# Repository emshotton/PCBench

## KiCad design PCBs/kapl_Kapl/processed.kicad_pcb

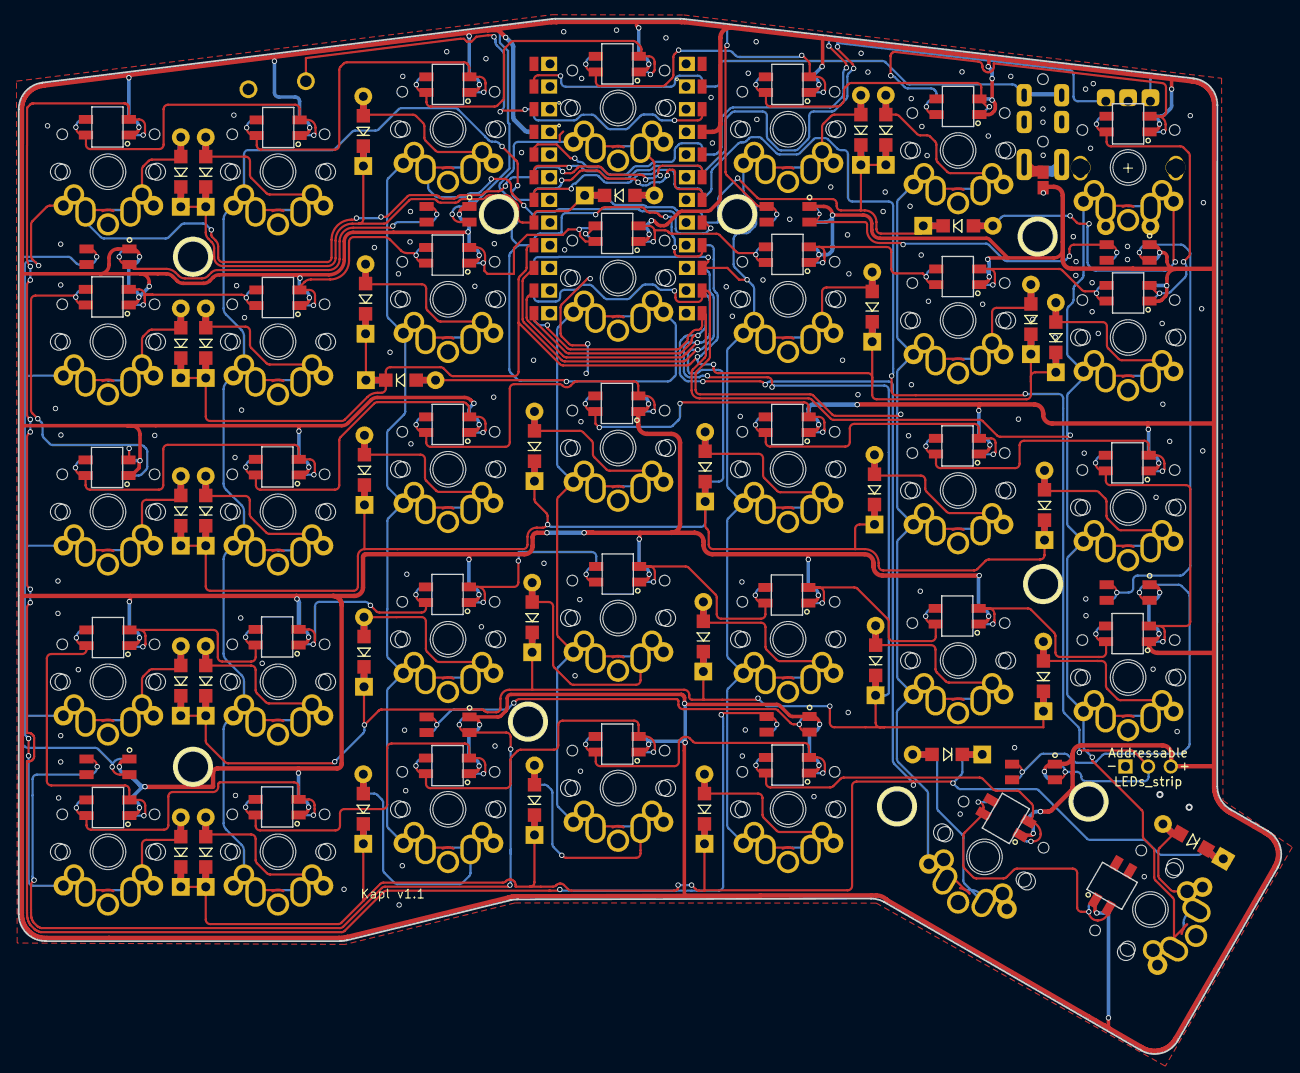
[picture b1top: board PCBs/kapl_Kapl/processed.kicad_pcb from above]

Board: 2 copper layers, 141.5 x 116.0 mm, 128 parts (0 on the bottom side), 97 nets.

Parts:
BL1, BL2, BL3, BL4, BL5, BL6, BL7, BL8, BL9: SK6812MINI; SK6812MINI_surface
D1, D2, D3, D4, D5, D6, D7, D8, D9, D10, D11, D12, D13, D14, D15, D16, D17, D18, D19, D20, D21, D22, D23, D24, D25, D26, D27, D28, D29, D30, D31, D32, D33, D34, D35: Diode
E_SW1: RotaryEncoder_Switch; RotaryEncoder_Alps_EC11E-Switch_Vertical_H20mm
H1, H2, H3, H4, H5, H6, H7, H8, H9: MountingHole; MountingHole_3.2mm_M3
J1: LED_strip_conector; StripLED_rev
L1, L2, L3, L4, L5, L6, L7, L8, L9, L10, L11, L12, L13, L14, L15, L16, L17, L18, L19, L20, L21, L22, L23, L24, L25, L26, L27, L28, L29, L30, L31, L32, L33, L34, L35: SK6812MINI; SK6812MINI_rev
MJ1: Mini Jack; MJ-4PP-9
RSW1: SW_PUSH; ResetSW
SW1, SW2, SW3, SW4, SW5, SW6, SW8, SW9, SW10, SW11, SW12, SW13, SW14, SW15, SW16, SW17, SW18, SW19, SW20, SW21, SW22, SW23, SW24, SW25, SW26, SW27, SW28, SW29, SW30, SW31, SW32, SW33, SW34, SW35: SW_PUSH; MX-ALPs-PG1350-rev
SW7: SW_PUSH; MX-ALPs-PG1350-rev(for_encoder)
U1: ProMicro

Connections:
GND: BL1.2 (GND), BL2.2 (GND), BL3.2 (GND), BL4.2 (GND), BL5.2 (GND), BL6.2 (GND), BL7.2 (GND), BL8.2 (GND), BL9.2 (GND), E_SW1.C, J1.1, L1.2 (GND), L2.2 (GND), L3.2 (GND), L4.2 (GND), L5.2 (GND), L6.2 (GND), L7.2 (GND), L8.2 (GND), L9.2 (GND), L10.2 (GND), L11.2 (GND), L12.2 (GND), L13.2 (GND), L14.2 (GND), L15.2 (GND), L16.2 (GND), L17.2 (GND), L18.2 (GND), L19.2 (GND), L20.2 (GND), L21.2 (GND), L22.2 (GND), L23.2 (GND), L24.2 (GND), L25.2 (GND), L26.2 (GND), L27.2 (GND), L28.2 (GND), L29.2 (GND), L30.2 (GND), L31.2 (GND), L32.2 (GND), L33.2 (GND), L34.2 (GND), L35.2 (GND), MJ1.C, RSW1.2, U1.3 (GND), U1.4 (GND), U1.23 (GND)
LED: BL1.3 (DIN), J1.2, U1.7 (D4)
unnamed: BL1.1 (DOUT), BL2.3 (DIN)
unnamed: BL2.1 (DOUT), BL3.3 (DIN)
unnamed: BL3.1 (DOUT), BL4.3 (DIN)
unnamed: BL4.1 (DOUT), BL5.3 (DIN)
unnamed: BL5.1 (DOUT), BL6.3 (DIN)
unnamed: BL6.1 (DOUT), BL7.3 (DIN)
unnamed: BL7.1 (DOUT), BL8.3 (DIN)
unnamed: BL8.1 (DOUT), BL9.3 (DIN)
unnamed: BL9.1 (DOUT), L1.3 (DIN)
unnamed: D1.2 (A), SW1.2
unnamed: D2.2 (A), SW2.2
unnamed: D3.2 (A), SW3.2
unnamed: D4.2 (A), SW4.2
unnamed: D5.2 (A), SW5.2
unnamed: D6.2 (A), SW6.2
unnamed: D7.2 (A), E_SW1.S1, SW7.2
unnamed: D8.2 (A), SW8.2
unnamed: D9.2 (A), SW9.2
unnamed: D10.2 (A), SW10.2
unnamed: D11.2 (A), SW11.2
unnamed: D12.2 (A), SW12.2
unnamed: D13.2 (A), SW13.2
unnamed: D14.2 (A), SW14.2
unnamed: D15.2 (A), SW15.2
unnamed: D16.2 (A), SW16.2
unnamed: D17.2 (A), SW17.2
unnamed: D18.2 (A), SW18.2
unnamed: D19.2 (A), SW19.2
unnamed: D20.2 (A), SW20.2
unnamed: D21.2 (A), SW21.2
unnamed: D22.2 (A), SW22.2
unnamed: D23.2 (A), SW23.2
unnamed: D24.2 (A), SW24.2
unnamed: D25.2 (A), SW25.2
unnamed: D26.2 (A), SW26.2
unnamed: D27.2 (A), SW27.2
unnamed: D28.2 (A), SW28.2
unnamed: D29.2 (A), SW29.2
unnamed: D30.2 (A), SW30.2
unnamed: D31.2 (A), SW31.2
unnamed: D32.2 (A), SW32.2
unnamed: D33.2 (A), SW33.2
unnamed: D34.2 (A), SW34.2
unnamed: D35.2 (A), SW35.2
unnamed: L1.1 (DOUT), L2.3 (DIN)
unnamed: L2.1 (DOUT), L3.3 (DIN)
unnamed: L3.1 (DOUT), L4.3 (DIN)
unnamed: L4.1 (DOUT), L5.3 (DIN)
unnamed: L5.1 (DOUT), L6.3 (DIN)
unnamed: L6.1 (DOUT), L7.3 (DIN)
unnamed: L8.3 (DIN), L9.1 (DOUT)
unnamed: L9.3 (DIN), L10.1 (DOUT)
unnamed: L10.3 (DIN), L11.1 (DOUT)
unnamed: L11.3 (DIN), L12.1 (DOUT)
unnamed: L12.3 (DIN), L13.1 (DOUT)
unnamed: L13.3 (DIN), L14.1 (DOUT)
unnamed: L7.1 (DOUT), L14.3 (DIN)
unnamed: L15.1 (DOUT), L16.3 (DIN)
unnamed: L8.1 (DOUT), L15.3 (DIN)
unnamed: L16.1 (DOUT), L17.3 (DIN)
unnamed: L17.1 (DOUT), L18.3 (DIN)
unnamed: L18.1 (DOUT), L19.3 (DIN)
unnamed: L19.1 (DOUT), L20.3 (DIN)
unnamed: L20.1 (DOUT), L21.3 (DIN)
unnamed: L21.1 (DOUT), L28.3 (DIN)
unnamed: L22.1 (DOUT), L29.3 (DIN)
unnamed: L22.3 (DIN), L23.1 (DOUT)
unnamed: L23.3 (DIN), L24.1 (DOUT)
unnamed: L24.3 (DIN), L25.1 (DOUT)
unnamed: L25.3 (DIN), L26.1 (DOUT)
unnamed: L26.3 (DIN), L27.1 (DOUT)
unnamed: L27.3 (DIN), L28.1 (DOUT)
unnamed: L29.1 (DOUT), L30.3 (DIN)
unnamed: L30.1 (DOUT), L31.3 (DIN)
unnamed: L31.1 (DOUT), L32.3 (DIN)
unnamed: L32.1 (DOUT), L33.3 (DIN)
unnamed: L33.1 (DOUT), L34.3 (DIN)
unnamed: L34.1 (DOUT), L35.3 (DIN)
VCC: BL1.4 (VDD), BL2.4 (VDD), BL3.4 (VDD), BL4.4 (VDD), BL5.4 (VDD), BL6.4 (VDD), BL7.4 (VDD), BL8.4 (VDD), BL9.4 (VDD), J1.3, L1.4 (VDD), L2.4 (VDD), L3.4 (VDD), L4.4 (VDD), L5.4 (VDD), L6.4 (VDD), L7.4 (VDD), L8.4 (VDD), L9.4 (VDD), L10.4 (VDD), L11.4 (VDD), L12.4 (VDD), L13.4 (VDD), L14.4 (VDD), L15.4 (VDD), L16.4 (VDD), L17.4 (VDD), L18.4 (VDD), L19.4 (VDD), L20.4 (VDD), L21.4 (VDD), L22.4 (VDD), L23.4 (VDD), L24.4 (VDD), L25.4 (VDD), L26.4 (VDD), L27.4 (VDD), L28.4 (VDD), L29.4 (VDD), L30.4 (VDD), L31.4 (VDD), L32.4 (VDD), L33.4 (VDD), L34.4 (VDD), L35.4 (VDD), MJ1.D, U1.21 (VCC)
col0: SW1.1, SW8.1, SW15.1, SW22.1, SW29.1, U1.19 (F5)
col1: SW2.1, SW9.1, SW16.1, SW23.1, SW30.1, U1.18 (F6)
col2: SW3.1, SW10.1, SW17.1, SW24.1, SW31.1, U1.17 (F7)
col3: SW4.1, SW11.1, SW18.1, SW25.1, SW32.1, U1.16 (B1)
col4: SW5.1, SW12.1, SW19.1, SW26.1, SW33.1, U1.15 (B3)
col5: SW6.1, SW13.1, SW20.1, SW27.1, SW34.1, U1.14 (B2)
col6: E_SW1.S2, SW7.1, SW14.1, SW21.1, SW28.1, SW35.1, U1.13 (B6)
data: MJ1.B, U1.2 (RX)
encoder_A: E_SW1.A, U1.5 (SDA)
encoder_B: E_SW1.B, U1.6 (SCL)
reset: RSW1.1, U1.22 (RST)
row0: D1.1 (K), D2.1 (K), D3.1 (K), D4.1 (K), D5.1 (K), D6.1 (K), D7.1 (K), U1.8 (C6)
row1: D8.1 (K), D9.1 (K), D10.1 (K), D11.1 (K), D12.1 (K), D13.1 (K), D14.1 (K), U1.9 (D7)
row2: D15.1 (K), D16.1 (K), D17.1 (K), D18.1 (K), D19.1 (K), D20.1 (K), D21.1 (K), U1.10 (E6)
row3: D22.1 (K), D23.1 (K), D24.1 (K), D25.1 (K), D26.1 (K), D27.1 (K), D28.1 (K), U1.11 (B4)
row4: D29.1 (K), D30.1 (K), D31.1 (K), D32.1 (K), D33.1 (K), D34.1 (K), D35.1 (K), U1.12 (B5)

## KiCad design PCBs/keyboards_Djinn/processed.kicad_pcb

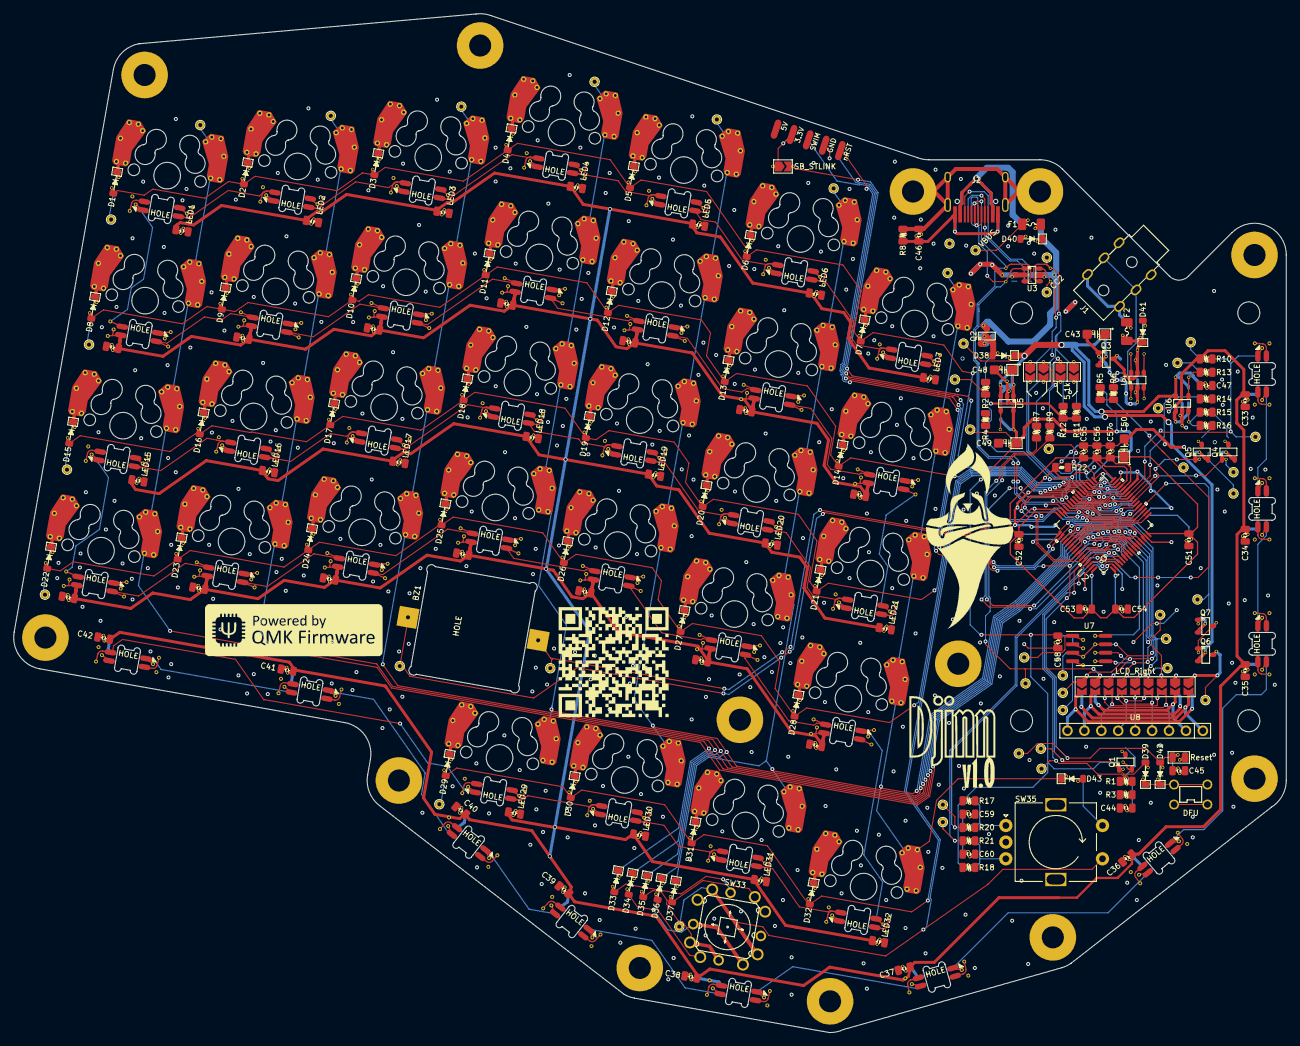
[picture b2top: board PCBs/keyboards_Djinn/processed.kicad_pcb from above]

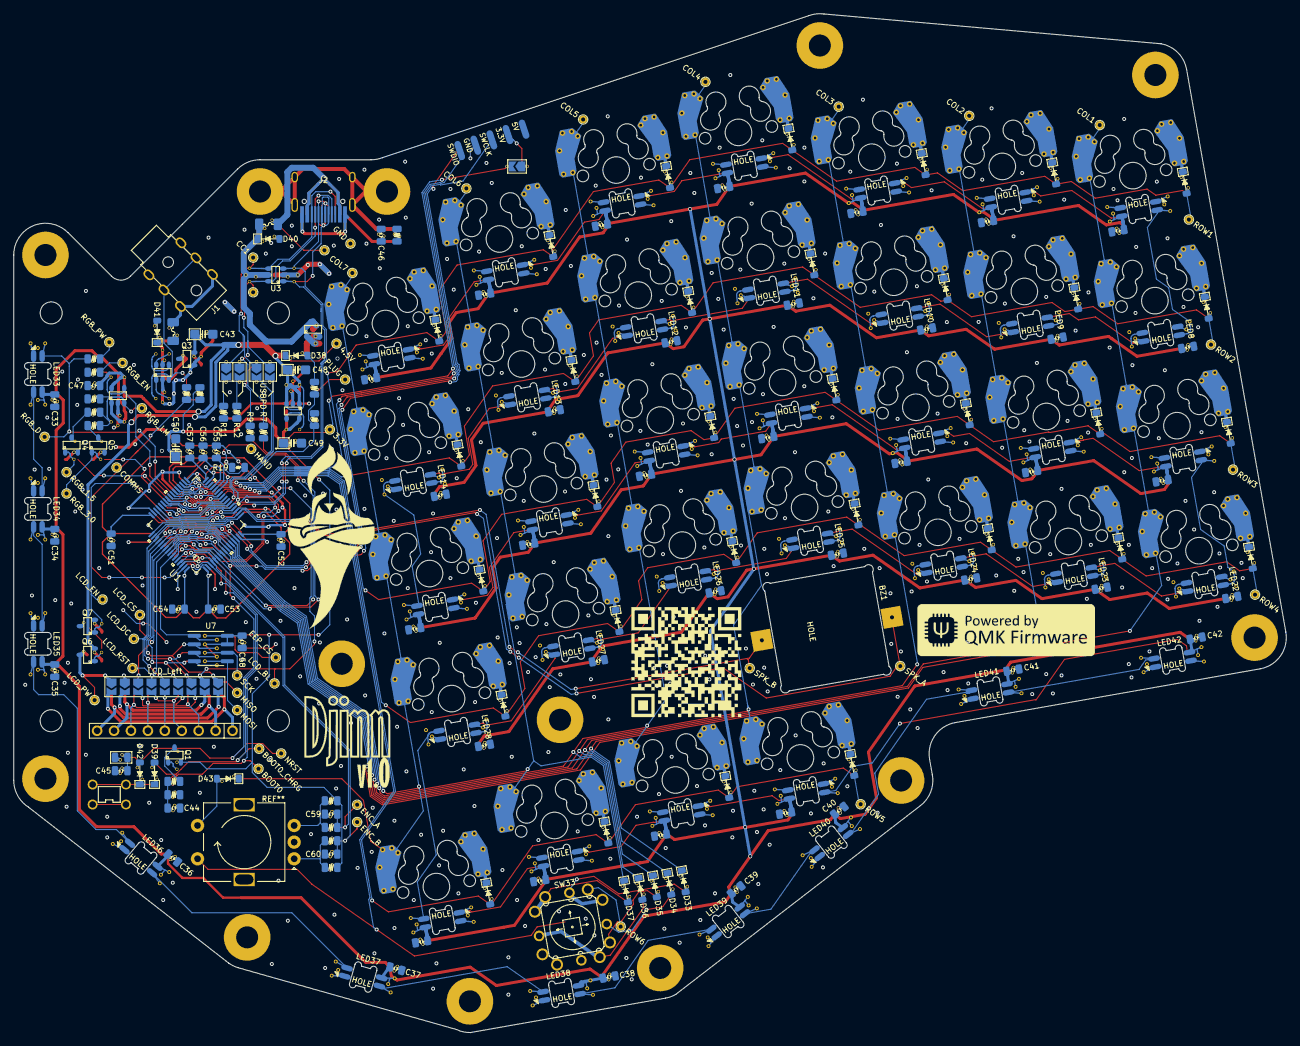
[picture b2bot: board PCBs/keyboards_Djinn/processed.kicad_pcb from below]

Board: 2 copper layers, 191.0 x 152.9 mm, 283 parts (38 on the bottom side), 163 nets.

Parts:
BZ1: KLJ-1625; Piezo-KLJ-1625
C1, C2, C3, C4, C5, C6, C7, C8, C9, C10, C11, C12, C13, C14, C15, C16, C17, C18, C19, C20, C21, C22, C23, C24, C25, C26, C27, C28, C29, C30, C31, C32: 100n; MX-1U-Cap0805
C33, C34, C35, C36, C37, C38, C39, C40, C41, C42, C44, C45, C47, C51, C52, C53, C54, C55, C56, C57, C58, C59, C60: 100n; C-0805_2012Metric
C43, C48, C49, C50: 10u; CP_3216
C46: 4.7n; C-0805_2012Metric
D1, D2, D3, D4, D5, D6, D7, D8, D9, D10, D11, D12, D13, D14, D15, D16, D17, D18, D19, D20, D21, D22, D23, D24, D25, D26, D27, D28, D29, D30, D31, D32: 1N4148; MX-1U-D_SOD-123
D33, D34, D35, D36, D37, D39, D42, D43: 1N4148; D_SOD-123
D38: SS34; D_SOD-123
D40, D41: SMF5.0CA; D_SOD-123
F1: 3.0A 1206 Polyfuse; Fuse_1206_3216Metric
F2: 1.5A 1206 Polyfuse; Fuse_1206_3216Metric
J1: AudioJack3; PJ-3136-B
J2: USB-C-2.0; HRO-TYPE-C-31-M-12-HandSoldering-NoSBU
J3: ST-Link Clone; STLink_SideSocket
J4: LCD_Left; SolderJumper-1.0x1.5mm_x9
J5: LCD_Right; SolderJumper-1.0x1.5mm_x9
JP1: Reset; JumperPads
LED1, LED2, LED3, LED4, LED5, LED6, LED7, LED8, LED9, LED10, LED11, LED12, LED13, LED14, LED15, LED16, LED17, LED18, LED19, LED20, LED21, LED22, LED23, LED24, LED25, LED26, LED27, LED28, LED29, LED30, LED31, LED32: MX-1U-SK6812Mini-E
LED33, LED34, LED35, LED36, LED37, LED38, LED39, LED40, LED41, LED42: SK6812Mini-E
LOGO1, LOGO2: QMK Logo; QMK_PoweredBy
LOGO3, LOGO4: Djinn Logo; DjinnLogo
LOGO5, LOGO6: Djinn Name+Ver; DjinnNameVer
LOGO7, LOGO8: QMK QRCode; QMK_QRCode
OUTLINE1: Outline Footprint; Djinn_MainPCB
Q1: MMUN2133LT1G; SOT-23-3
Q2, Q3, Q6: AO3401A; SOT-23-3
Q4, Q5, Q7: MMUN2233LT1G; SOT-23-3
R1, R6: 120; R-0805_2012Metric
R2, R10, R11, R12: 5.1k; R-0805_2012Metric
R3, R8: 1M; R-0805_2012Metric
R4: 100k; R-0805_2012Metric
R5: 1.5k; R-0805_2012Metric
R7, R9, R13, R16, R17, R18, R19, R20, R21, R22: 9.1k; R-0805_2012Metric
R14: 52.3k; R-0805_2012Metric
R15: 13.7k; R-0805_2012Metric
SB1: 5.1k; SolderJumper-1.0x1.5mm_x2
SB2: USBPD; SolderJumper-1.0x1.5mm_x2
SB3: SB_STLINK; SolderJumper-1.0x1.5mm
SW1, SW2, SW3, SW4, SW5, SW6, SW7, SW8, SW9, SW10, SW11, SW12, SW13, SW14, SW15, SW16, SW17, SW18, SW19, SW20, SW21, SW22, SW23, SW24, SW25, SW26, SW27, SW28, SW29, SW30, SW31, SW32: SW_Push; MX-1U-Hotswap
SW33: 5Way-Tactile_K1-1506DN-01; 5Way-K1-1506DN-01
SW34: DFU; PushButton_4.5mm
SW35: Rotary_Encoder_Switch; EC11_Switch
TP1: GND; TestPoint
TP2: SCK; TestPoint
TP3: VBUS; TestPoint
TP4: MISO; TestPoint
TP5: 4.5V; TestPoint
TP6: MOSI; TestPoint
TP7: 3.3V; TestPoint
TP8: NRST; TestPoint
TP9: COL1; TestPoint
TP10: BOOT0; TestPoint
TP11: COL2; TestPoint
TP12: BOOT0_CHRG; TestPoint
TP13: COL3; TestPoint
TP14: COMMS; TestPoint
TP15: COL4; TestPoint
TP16: COL5; TestPoint
TP17: RGB_PW; TestPoint
TP18: COL6; TestPoint
TP19: RGB_EN; TestPoint
TP20: COL7; TestPoint
TP21: RGB_D; TestPoint
TP22: RGB_1.5; TestPoint
TP23: ROW1; TestPoint
TP24: RGB_3.0; TestPoint
TP25: ROW2; TestPoint
TP26: RGB_LM; TestPoint
TP27: ROW3; TestPoint
TP28: ROW4; TestPoint
TP29: LCD_PW; TestPoint
TP30: ROW5; TestPoint
TP31: LCD_EN; TestPoint
TP32: ROW6; TestPoint
TP33: LCD_CS; TestPoint
TP34: LCD_DC; TestPoint
TP35: SPK_A; TestPoint
TP36: LCD_RST; TestPoint
TP37: SPK_B; TestPoint
TP38: LCD_BL; TestPoint
TP39: CC1; TestPoint
TP40: EEP_CS; TestPoint
TP41: CC2; TestPoint
TP42: HAND; TestPoint
TP43: PLUG; TestPoint
TP44: ENC_A; TestPoint
TP45: ENC_B; TestPoint
U1, U2: STM32G474RETx
U3, U4: USBLC6-4SC6; SOT-23-6
U5: AP2127K-3.3; SOT-23-5
U6: MT9700; SOT-23-5
U7: MB85RS64; SOIC-8_3.9x4.9mm_P1.27mm
U8: LCD-ILI9341-2.2in

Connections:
+3V3: C49.1, C50.1, C51.1, C52.1, C53.1, C54.1, C55.1, C56.1, C57.1, C58.1, Q1.2, R5.2, R17.1, R18.1, R19.1, SB3.2, TP7.1, U1.1, U1.16, U1.28, U1.29, U1.32, U1.48, U1.64, U2.1, U2.16, U2.28, U2.29, U2.32, U2.48, U2.64, U5.5, U7.3, U7.7, U7.8
/VBUS_BLOCKED: D38.2, Q2.2, R2.1
/VBUS_FUSED: D40.1, F1.1, Q2.3, U3.5
/VBUS_TRS: F2.2, J1.T
/VBUS_TRS_FUSED: D41.1, F2.1, Q3.3, U4.5
BOOT0: C44.1, R1.1, R3.1, TP10.1, U1.61, U2.61
BOOT0_CHRG: D39.2, Q1.1, TP12.1, U1.60, U2.60
CC1: J2.B5, R9.2, SB1.3, SB2.1, TP39.1, U3.4
CC2: J2.A5, R7.2, SB1.1, SB2.3, TP41.1, U3.6
COL1: SW1.2, SW8.2, SW15.2, SW22.2, TP9.1, U1.8, U2.8
COL2: D33.1, SW2.2, SW9.2, SW16.2, SW23.2, TP11.1, U1.9, U2.9
COL3: D34.1, SW3.2, SW10.2, SW17.2, SW24.2, TP13.1, U1.10, U2.10
COL4: D35.1, SW4.2, SW11.2, SW18.2, SW25.2, SW29.2, TP15.1, U1.11, U2.11
COL5: D36.1, SW5.2, SW12.2, SW19.2, SW26.2, SW30.2, TP16.1, U1.12, U2.12
COL6: D37.1, SW6.2, SW13.2, SW20.2, SW27.2, SW31.2, TP18.1, U1.13, U2.13
COL7: D43.1, SW7.2, SW14.2, SW21.2, SW28.2, SW32.2, TP20.1, U1.14, U2.14
CURR_1500mA_OK: Q4.1, TP22.1, U1.24, U2.24
CURR_3000mA_OK: Q5.1, TP24.1, U1.23, U2.23
CURR_LIM: R14.1, R15.1, R16.1, TP26.1, U6.3
D+: J2.A6, J2.B6, U1.46, U2.46, U3.3
D-: J2.A7, J2.B7, U1.45, U2.45, U3.1
EEP_CS: TP40.1, U1.58, U2.58, U7.1
ENC_A: C59.1, R20.1, TP44.1, U1.3, U2.3
ENC_B: C60.1, R21.1, TP45.1, U1.4, U2.4
GND: C1.2, C2.2, C3.2, C4.2, C5.2, C6.2, C7.2, C8.2, C9.2, C10.2, C11.2, C12.2, C13.2, C14.2, C15.2, C16.2, C17.2, C18.2, C19.2, C20.2, C21.2, C22.2, C23.2, C24.2, C25.2, C26.2, C27.2, C28.2, C29.2, C30.2, C31.2, C32.2, C33.2, C34.2, C35.2, C36.2, C37.2, C38.2, C39.2, C40.2, C41.2, C42.2, C43.2, C44.2, C45.2, C46.2, C47.2, C48.2, C49.2, C50.2, C51.2, C52.2, C53.2, C54.2, C55.2, C56.2, C57.2, C58.2, C59.2, C60.2, D40.2, D41.2, J1.S, J2.A1, J2.B1, J3.3, J3.4, J4.3, J5.15, JP1.2, LED1.3, LED2.3, LED3.3, LED4.3, LED5.3, LED6.3, LED7.3, LED8.3, LED9.3, LED10.3, LED11.3, LED12.3, LED13.3, LED14.3, LED15.3, LED16.3, LED17.3, LED18.3, LED19.3, LED20.3, LED21.3, LED22.3, LED23.3, LED24.3, LED25.3, LED26.3, LED27.3, LED28.3, LED29.3, LED30.3, LED31.3, LED32.3, LED33.3, LED34.3, LED35.3, LED36.3, LED37.3, LED38.3, LED39.3, LED40.3, LED41.3, LED42.3, Q2.1, Q3.1, Q4.2, Q5.2, Q7.2, R3.2, R4.1, R8.2, R11.2, R12.2, R13.2, R14.2, R22.1, SW34.1, SW35.C, TP1.1, U1.15, U1.27, U1.31, U1.47, U1.63, U2.15, U2.27, U2.31, U2.47, U2.63, U3.2, U4.2, U5.2, U6.2, U7.4
LCD_BL_PWM: J4.15, J5.3, TP38.1, U1.21, U2.21
LCD_CS: J4.5, J5.13, TP33.1, U1.55, U2.55
LCD_DC: J4.9, J5.9, TP34.1, U1.51, U2.51
LCD_EN: Q7.1, TP31.1, U1.20, U2.20
LCD_L1_R9: J4.2, J5.2, U8.9
LCD_L2_R8: J4.4, J5.4, U8.8
LCD_L3_R7: J4.6, J5.6, U8.7
LCD_L4_R6: J4.8, J5.8, U8.6
LCD_L5_R5: J4.10, J5.10, U8.5
LCD_L6_R4: J4.12, J5.12, U8.4
LCD_L7_R3: J4.14, J5.14, U8.3
LCD_L8_R2: J4.16, J5.16, U8.2
LCD_L9_R1: J4.18, J5.18, U8.1
LCD_PWR: J4.1, J5.17, Q6.3, TP29.1
LCD_RST: J4.7, J5.11, TP36.1, U1.56, U2.56
MISO: J4.17, J5.1, TP4.1, U1.53, U2.53, U7.2
MOSI: J4.11, J5.7, TP6.1, U1.54, U2.54, U7.5
NRST: C45.1, D42.2, J3.1, JP1.1, TP8.1, U1.7, U2.7
unnamed: D1.1, SW1.1
unnamed: D2.1, SW2.1
unnamed: D3.1, SW3.1
unnamed: D4.1, SW4.1
unnamed: D5.1, SW5.1
unnamed: D6.1, SW6.1
unnamed: D7.1, SW7.1
unnamed: D8.1, SW8.1
unnamed: D9.1, SW9.1
unnamed: D10.1, SW10.1
unnamed: D11.1, SW11.1
unnamed: D12.1, SW12.1
unnamed: D13.1, SW13.1
unnamed: D14.1, SW14.1
unnamed: D15.1, SW15.1
unnamed: D16.1, SW16.1
unnamed: D17.1, SW17.1
unnamed: D18.1, SW18.1
unnamed: D19.1, SW19.1
unnamed: D20.1, SW20.1
unnamed: D21.1, SW21.1
unnamed: D22.1, SW22.1
unnamed: D23.1, SW23.1
unnamed: D24.1, SW24.1
unnamed: D25.1, SW25.1
unnamed: D26.1, SW26.1
unnamed: D27.1, SW27.1
unnamed: D28.1, SW28.1
unnamed: D29.1, SW29.1
unnamed: D30.1, SW30.1
unnamed: D31.1, SW31.1
unnamed: D32.1, SW32.1
unnamed: D33.2, SW33.1
unnamed: D34.2, SW33.2
unnamed: D35.2, SW33.3
unnamed: D36.2, SW33.5
unnamed: D37.2, SW33.6
unnamed: D39.1, D42.1, SW34.2
unnamed: D43.2, SW35.S2
unnamed: J1.R, R6.2, U4.3
unnamed: J3.7, J3.8, SB3.1
unnamed: LED1.2, LED2.4
unnamed: LED1.4, LED8.2
unnamed: LED2.2, LED3.4
unnamed: LED3.2, LED4.4
unnamed: LED4.2, LED5.4
unnamed: LED5.2, LED6.4
unnamed: LED6.2, LED7.4
unnamed: LED8.4, LED9.2
unnamed: LED9.4, LED10.2
unnamed: LED10.4, LED11.2
unnamed: LED11.4, LED12.2
unnamed: LED12.4, LED13.2
unnamed: LED13.4, LED14.2
unnamed: LED14.4, LED21.2
unnamed: LED15.2, LED16.4
unnamed: LED15.4, LED22.2
unnamed: LED16.2, LED17.4
unnamed: LED17.2, LED18.4
unnamed: LED18.2, LED19.4
unnamed: LED19.2, LED20.4
unnamed: LED20.2, LED21.4
unnamed: LED22.4, LED23.2
unnamed: LED23.4, LED24.2
unnamed: LED24.4, LED25.2
unnamed: LED25.4, LED26.2
unnamed: LED26.4, LED27.2
unnamed: LED27.4, LED28.2
unnamed: LED28.4, LED32.2
unnamed: LED29.2, LED30.4
unnamed: LED30.2, LED31.4
unnamed: LED31.2, LED32.4
unnamed: LED33.2, LED34.4
unnamed: LED34.2, LED35.4
unnamed: LED35.2, LED36.4
unnamed: LED36.2, LED37.4
unnamed: LED37.2, LED38.4
unnamed: LED38.2, LED39.4
unnamed: LED39.2, LED40.4
unnamed: LED40.2, LED41.4
unnamed: LED41.2, LED42.4
unnamed: Q1.3, R1.2
unnamed: Q4.3, R15.2
unnamed: Q5.3, R16.2
unnamed: Q6.1, Q7.3
unnamed: R7.1, U1.5, U2.5
unnamed: R9.1, U1.6, U2.6
unnamed: R11.1, SB1.4
unnamed: R12.1, SB1.2
unnamed: U1.2, U2.2
unnamed: U1.17, U2.17
unnamed: U1.22, U2.22
unnamed: U1.30, U2.30
unnamed: U1.41, U2.41
unnamed: U1.42, U2.42
PIEZO_A: BZ1.1, TP35.1, U1.18, U2.18
PIEZO_B: BZ1.2, TP37.1, U1.19, U2.19
PLUG_DETECT: R2.2, R4.2, TP43.1, U1.34, U2.34
Pre-Shield: C46.1, J2.S1, OUTLINE1.1, R8.1
ROT_A: R17.2, R20.2, SW35.A
ROT_B: R18.2, R21.2, SW35.B
ROW1: D1.2, D2.2, D3.2, D4.2, D5.2, D6.2, D7.2, TP23.1, U1.35, U2.35
ROW2: D8.2, D9.2, D10.2, D11.2, D12.2, D13.2, D14.2, TP25.1, U1.36, U2.36
ROW3: D15.2, D16.2, D17.2, D18.2, D19.2, D20.2, D21.2, TP27.1, U1.37, U2.37
ROW4: D22.2, D23.2, D24.2, D25.2, D26.2, D27.2, D28.2, TP28.1, U1.38, U2.38
ROW5: D29.2, D30.2, D31.2, D32.2, TP30.1, U1.39, U2.39
ROW6: SW33.4, SW35.S1, TP32.1, U1.40, U2.40
SCK: J4.13, J5.5, TP2.1, U1.52, U2.52, U7.6
SK6812_EN: R13.1, TP19.1, U1.25, U2.25, U6.4
SK6812_MTRX_IN: LED29.4, LED42.2
SK6812_PWM: LED33.4, R10.2, TP21.1, U1.26, U2.26
SK6812_PWR: C1.1, C2.1, C3.1, C4.1, C5.1, C6.1, C7.1, C8.1, C9.1, C10.1, C11.1, C12.1, C13.1, C14.1, C15.1, C16.1, C17.1, C18.1, C19.1, C20.1, C21.1, C22.1, C23.1, C24.1, C25.1, C26.1, C27.1, C28.1, C29.1, C30.1, C31.1, C32.1, C33.1, C34.1, C35.1, C36.1, C37.1, C38.1, C39.1, C40.1, C41.1, C42.1, LED1.1, LED2.1, LED3.1, LED4.1, LED5.1, LED6.1, LED7.1, LED8.1, LED9.1, LED10.1, LED11.1, LED12.1, LED13.1, LED14.1, LED15.1, LED16.1, LED17.1, LED18.1, LED19.1, LED20.1, LED21.1, LED22.1, LED23.1, LED24.1, LED25.1, LED26.1, LED27.1, LED28.1, LED29.1, LED30.1, LED31.1, LED32.1, LED33.1, LED34.1, LED35.1, LED36.1, LED37.1, LED38.1, LED39.1, LED40.1, LED41.1, LED42.1, R10.1, TP17.1, U6.1
SPLIT_COMMS: R5.1, R6.1, TP14.1, U1.62, U2.62
SPLIT_HAND_PIN: R19.2, R22.2, TP42.1, U1.33, U2.33
SWCLK: J3.6, U1.50, U2.50
SWDIO: J3.2, U1.49, U2.49
UCPD_CC1: SB2.2, U1.43, U1.59, U2.43, U2.59
UCPD_CC2: SB2.4, U1.44, U1.57, U2.44, U2.57
VDD: C43.1, C47.1, C48.1, D38.1, Q3.2, Q6.2, TP5.1, U5.1, U5.3, U6.5
V_USB: F1.2, J2.A4, J2.B4, TP3.1

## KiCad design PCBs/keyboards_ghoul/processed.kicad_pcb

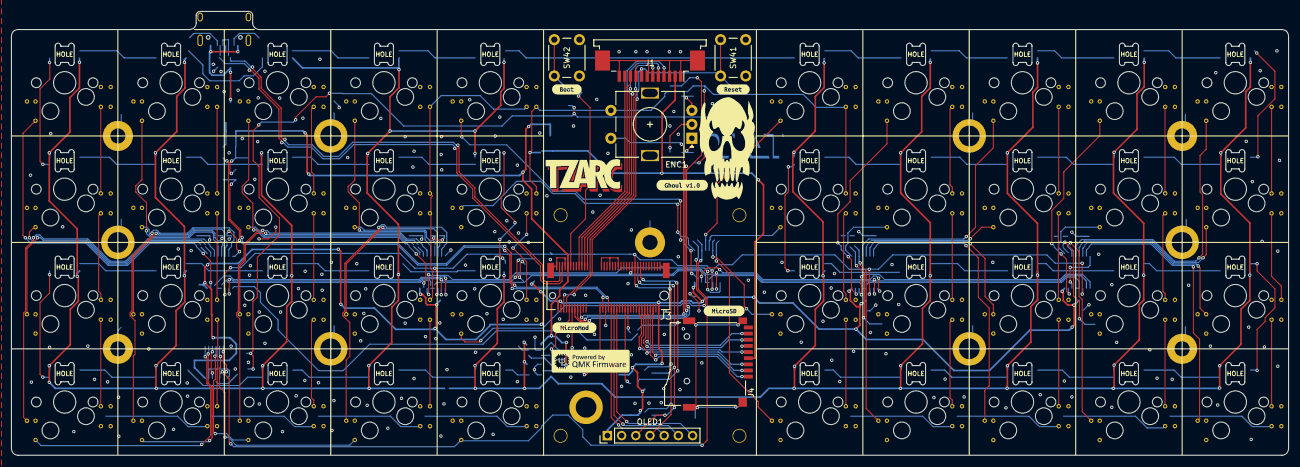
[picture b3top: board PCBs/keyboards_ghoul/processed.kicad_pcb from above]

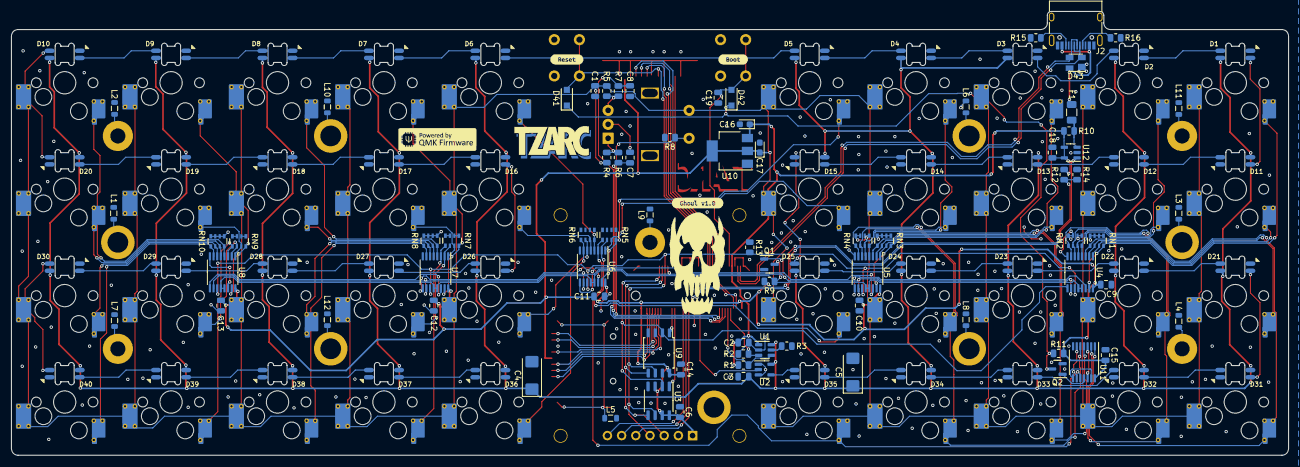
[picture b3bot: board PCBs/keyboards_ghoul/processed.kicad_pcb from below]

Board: 2 copper layers, 228.6 x 79.4 mm, 185 parts (88 on the bottom side), 148 nets.

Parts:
C1, C2, C3, C6, C7, C8, C9, C10, C11, C12, C13, C14, C15, C18, C19: 100n; C_0805_2012Metric
C4, C5: 100u; CP_EIA-6032-15_Kemet-U
C16, C17: 1u; CP_EIA-2012-15_AVX-P
D1, D2, D3, D4, D5, D6, D7, D8, D9, D10, D11, D12, D13, D14, D15, D16, D17, D18, D19, D20, D21, D22, D23, D24, D25, D26, D27, D28, D29, D30, D31, D32, D33, D34, D35, D36, D37, D38, D39, D40: SK6803; SK6803Mini-E
D41, D42: 1N4148WL; D_SOD-123F
D43: PRTR5V0U2X; SOT-143
ENC1: EC11N; RotaryEncoder_Alps_EC11E-Switch_Vertical_H20mm_Centred
F1: RF1989-000; Fuse_1206_3216Metric
H1, H3, H5, H7, H9, H11: L=2.5mm M2 Standoff; MountingHole_3.7mm_Pad
H2, H4, H6, H8, H10: M2 Screw; MountingHole_2.7mm_M2.5_Pad
J1: X10B25L12T; TE_1-84953-2_1x12-1MP_P1.0mm_Horizontal
J2: HRO_TYPE-C-31-M-12; USB_C_Receptacle_HRO_TYPE-C-31-M-12
J3: MICROMOD_E-2222; MicroMod_M.2-CONNECTOR-E
J4: microSD_TF-115; microSD_XunPu_TF-115
L1, L2, L3, L4, L5, L6, L7, L8, L9, L10, L11, L12: MPZ2012S101AT000; L_0805_2012Metric
NT1, NT2, NT3: NetTie-2_SMD_Pad0.2mm
OLED1: MTF185-107SY1; OLED_SSD1351_1.5inch
Q1, Q2: 2N7002; SOT-23
R1, R2, R4, R5, R6, R7, R8, R9, R11, R13, R15, R16: 5.1k; R_0805_2012Metric
R3, R12, R14: 75k; R_0805_2012Metric
R10: 0.005R; R_0805_2012Metric
RN1, RN2, RN3, RN4, RN5, RN6, RN7, RN8, RN9, RN10: 4x10k; R_Array_Convex_4x0603
SW1, SW2, SW3, SW4, SW5, SW6, SW7, SW8, SW9, SW10, SW11, SW12, SW13, SW14, SW15, SW16, SW17, SW18, SW19, SW20, SW21, SW22, SW23, SW24, SW25, SW26, SW27, SW28, SW29, SW30, SW31, SW32, SW33, SW34, SW35, SW36, SW37, SW38, SW39, SW40: MX; MX-1U-Hotswap
SW41: nRST; SW_PUSH_6mm
SW42: nBOOT; SW_PUSH_6mm
U1: TPS2553DBVR; SOT-23-6
U2: SN74AHCT1G125DBVR; SOT-23-5
U3: MB85RS64PNF-G-JNERE1; SO-8_3.9x4.9mm_P1.27mm
U4, U5, U6, U7, U8: MC74HC589ADTR2G; TSSOP-16_4.4x5mm_P0.65mm
U9: W25Q64JVSSIQ; SOIC-8_5.23x5.23mm_P1.27mm
U10: AZ1117H-3.3TRE1; SOT-223-3_TabPin2
U11: MC74HC08ADTR2G; TSSOP-14_4.4x5mm_P0.65mm
U12: INA180A4IDBVT; SOT-23-5
kibuzzard-62354CEE, kibuzzard-62354CEE#2: G***; kibuzzard-62354CEE
kibuzzard-62367B4C: G***; kibuzzard-62367B4C
kibuzzard-62367B65: G***; kibuzzard-62367B65
kibuzzard-62367BDD: G***; kibuzzard-62367BDD
kibuzzard-62367C14: G***; kibuzzard-62367C14
kibuzzard-62367E91: G***; kibuzzard-62367E91
kibuzzard-6236804E: G***; kibuzzard-6236804E

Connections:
5V_Post: C2.1, C16.1, J3.9 (USB_VIN), NT3.2, R1.1, R10.1, U1.1 (IN), U10.3 (VI)
5V_Pre: F1.1, NT2.2, R10.2
+3V3: C6.1, C9.1, C10.1, C11.1, C12.1, C13.1, C14.1, C15.1, C17.1, J1.2, J3.2 (3.3V), J3.74 (3.3V), J4.4 (VDD), NT1.2, OLED1.1 (VCC), R9.2, R11.2, U3.3 (~WP), U3.7 (~HOLD), U3.8 (VCC), U4.16 (VCC), U5.16 (VCC), U6.16 (VCC), U7.16 (VCC), U8.16 (VCC), U9.8 (VCC), U10.2 (VO), U11.14 (VCC)
/Matrix_1_2: U4.14 (SA/SerialIn), U5.9 (QH/SerialOut/MISO)
/Matrix_2_3: U5.14 (SA/SerialIn), U6.9 (QH/SerialOut/MISO)
/Matrix_3_4: U6.14 (SA/SerialIn), U7.9 (QH/SerialOut/MISO)
/Matrix_4_5: U7.14 (SA/SerialIn), U8.9 (QH/SerialOut/MISO)
/Matrix_Latch: Q1.3 (D), R9.1, U4.12 (Latch), U4.13 (SS/~PL), U5.12 (Latch), U5.13 (SS/~PL), U6.12 (Latch), U6.13 (SS/~PL), U7.12 (Latch), U7.13 (SS/~PL), U8.12 (Latch), U8.13 (SS/~PL)
CC1: J2.A5 (CC1), R16.2
CC2: J2.B5 (CC2), R15.2
CURR_LIM: R3.1, U1.5 (ILIM)
CURR_MEAS: J3.34 (A0), U12.1
D+: D43.3 (I/O2), J2.A6 (D+), J2.B6 (D+), J3.3 (USB_D+)
D-: D43.2 (I/O1), J2.A7 (D-), J2.B7 (D-), J3.5 (USB_D-)
DBG_RX_TGT_TX: J1.11, J3.17 (TX1)
DBG_TX_TGT_RX: J1.10, J3.19 (RX1)
EEPROM_CS: J3.50 (AUD_BCLK), U3.1 (~CS)
ENC_A: C7.1, J3.16 (I2C_~INT), R6.1
ENC_B: C8.1, J3.14 (I2C_SCL), R7.1
ENC_SW: ENC1.S2, J3.18 (D1/CAM_TRIG), R8.1
FLASH_CS: J3.52 (AUD_LRCLK), U9.1 (~CS)
GND: C1.2, C2.2, C3.2, C4.2, C5.2, C6.2, C7.2, C8.2, C9.2, C10.2, C11.2, C12.2, C13.2, C14.2, C15.2, C16.2, C17.2, C18.2, C19.2, D1.1 (VSS), D2.1 (VSS), D3.1 (VSS), D4.1 (VSS), D5.1 (VSS), D6.1 (VSS), D7.1 (VSS), D8.1 (VSS), D9.1 (VSS), D10.1 (VSS), D11.1 (VSS), D12.1 (VSS), D13.1 (VSS), D14.1 (VSS), D15.1 (VSS), D16.1 (VSS), D17.1 (VSS), D18.1 (VSS), D19.1 (VSS), D20.1 (VSS), D21.1 (VSS), D22.1 (VSS), D23.1 (VSS), D24.1 (VSS), D25.1 (VSS), D26.1 (VSS), D27.1 (VSS), D28.1 (VSS), D29.1 (VSS), D30.1 (VSS), D31.1 (VSS), D32.1 (VSS), D33.1 (VSS), D34.1 (VSS), D35.1 (VSS), D36.1 (VSS), D37.1 (VSS), D38.1 (VSS), D39.1 (VSS), D40.1 (VSS), D43.1 (GND), ENC1.C, J1.1, J1.3, J1.7, J1.9, J1.12, J1.MP (MountPin), J2.A1 (GND), J2.A12 (GND), J2.B1 (GND), J2.B12 (GND), J2.S1 (SHIELD), J3.1 (GND), J3.7 (GND), J3.33 (GND), J3.36 (GND), J3.39 (GND), J3.45 (GND), J3.75 (GND), J3.M (Mountpoint), J3.S (Screw), J4.6 (VSS), L1.2, L2.2, L3.2, L4.2, L5.2, L6.2, L7.2, L8.2, L9.2, L10.2, L11.2, L12.2, OLED1.2 (GND), Q1.2 (S), Q2.2 (S), R2.2, R3.2, R8.2, R13.1, R14.1, R15.1, R16.1, RN1.1 (R1.1), RN1.2 (R2.1), RN1.3 (R3.1), RN1.4 (R4.1), RN2.5 (R4.2), RN2.6 (R3.2), RN2.7 (R2.2), RN2.8 (R1.2), RN3.1 (R1.1), RN3.2 (R2.1), RN3.3 (R3.1), RN3.4 (R4.1), RN4.5 (R4.2), RN4.6 (R3.2), RN4.7 (R2.2), RN4.8 (R1.2), RN5.1 (R1.1), RN5.2 (R2.1), RN5.3 (R3.1), RN5.4 (R4.1), RN6.5 (R4.2), RN6.6 (R3.2), RN6.7 (R2.2), RN6.8 (R1.2), RN7.1 (R1.1), RN7.2 (R2.1), RN7.3 (R3.1), RN7.4 (R4.1), RN8.5 (R4.2), RN8.6 (R3.2), RN8.7 (R2.2), RN8.8 (R1.2), RN9.1 (R1.1), RN9.2 (R2.1), RN9.3 (R3.1), RN9.4 (R4.1), RN10.5 (R4.2), RN10.6 (R3.2), RN10.7 (R2.2), RN10.8 (R1.2), SW41.2, SW42.2, U1.2 (GND), U2.1, U2.3 (GND), U3.4 (GND), U4.8 (GND), U5.8 (GND), U6.8 (GND), U7.8 (GND), U8.8 (GND), U8.14 (SA/SerialIn), U9.4 (GND), U10.1 (GND), U11.7 (GND), U12.2 (GND)
Key_Pullup: C1.1, ENC1.S1, NT1.1, R4.1, R5.1, SW1.1, SW2.1, SW3.1, SW4.1, SW5.1, SW6.1, SW7.1, SW8.1, SW9.1, SW10.1, SW11.1, SW12.1, SW13.1, SW14.1, SW15.1, SW16.1, SW17.1, SW18.1, SW19.1, SW20.1, SW21.1, SW22.1, SW23.1, SW24.1, SW25.1, SW26.1, SW27.1, SW28.1, SW29.1, SW30.1, SW31.1, SW32.1, SW33.1, SW34.1, SW35.1, SW36.1, SW37.1, SW38.1, SW39.1, SW40.1
MATRIX_CS: J3.55 (SPI_~CS), Q1.1 (G), U4.10 (OutputEnable/~CS), U5.10 (OutputEnable/~CS), U6.10 (OutputEnable/~CS), U7.10 (OutputEnable/~CS), U8.10 (OutputEnable/~CS)
MISO: J3.61 (SPI_MISO), U3.2 (MISO), U4.9 (QH/SerialOut/MISO), U9.2 (DO(IO1))
MOSI: J3.59 (SPI_MOSI), OLED1.3 (MOSI), U3.5 (MOSI), U9.5 (DI(IO0))
unnamed: C18.1, NT3.1, R12.2, U12.4 (-), U12.5 (V+)
unnamed: D1.2 (DIN), D11.4 (DOUT)
unnamed: D1.4 (DOUT), D2.2 (DIN)
unnamed: D2.4 (DOUT), D3.2 (DIN)
unnamed: D3.4 (DOUT), D4.2 (DIN)
unnamed: D4.4 (DOUT), D5.2 (DIN)
unnamed: D5.4 (DOUT), D6.2 (DIN)
unnamed: D6.4 (DOUT), D7.2 (DIN)
unnamed: D7.4 (DOUT), D8.2 (DIN)
unnamed: D8.4 (DOUT), D9.2 (DIN)
unnamed: D9.4 (DOUT), D10.2 (DIN)
unnamed: D10.4 (DOUT), D20.2 (DIN)
unnamed: D11.2 (DIN), D12.4 (DOUT)
unnamed: D12.2 (DIN), D13.4 (DOUT)
unnamed: D13.2 (DIN), D14.4 (DOUT)
unnamed: D14.2 (DIN), D15.4 (DOUT)
unnamed: D15.2 (DIN), D25.4 (DOUT)
unnamed: D16.2 (DIN), D17.4 (DOUT)
unnamed: D16.4 (DOUT), D26.2 (DIN)
unnamed: D17.2 (DIN), D18.4 (DOUT)
unnamed: D18.2 (DIN), D19.4 (DOUT)
unnamed: D19.2 (DIN), D20.4 (DOUT)
unnamed: D21.2 (DIN), D31.4 (DOUT)
unnamed: D21.4 (DOUT), D22.2 (DIN)
unnamed: D22.4 (DOUT), D23.2 (DIN)
unnamed: D23.4 (DOUT), D24.2 (DIN)
unnamed: D24.4 (DOUT), D25.2 (DIN)
unnamed: D26.4 (DOUT), D27.2 (DIN)
unnamed: D27.4 (DOUT), D28.2 (DIN)
unnamed: D28.4 (DOUT), D29.2 (DIN)
unnamed: D29.4 (DOUT), D30.2 (DIN)
unnamed: D30.4 (DOUT), D40.2 (DIN)
unnamed: D31.2 (DIN), D32.4 (DOUT)
unnamed: D32.2 (DIN), D33.4 (DOUT)
unnamed: D33.2 (DIN), D34.4 (DOUT)
unnamed: D34.2 (DIN), D35.4 (DOUT)
unnamed: D36.2 (DIN), D37.4 (DOUT)
unnamed: D37.2 (DIN), D38.4 (DOUT)
unnamed: D38.2 (DIN), D39.4 (DOUT)
unnamed: D39.2 (DIN), D40.4 (DOUT)
unnamed: D41.1 (K), D42.1 (K), Q2.3 (D), R11.1
unnamed: H1.1, L1.1
unnamed: H2.1, L2.1
unnamed: H3.1, L3.1
unnamed: H4.1, L4.1
unnamed: H5.1, L6.1
unnamed: H6.1, L7.1
unnamed: H7.1, L8.1
unnamed: H8.1, L9.1
unnamed: H9.1, L10.1
unnamed: H10.1, L11.1
unnamed: H11.1, L12.1
unnamed: J4.S (SHIELD), L5.1
unnamed: NT2.1, U12.3 (+)
unnamed: Q2.1 (G), U11.11 (4Y)
OLED_CS: J3.40 (G0/BUS0), OLED1.5 (~CS)
OLED_DC: J3.42 (G1/BUS1), OLED1.6 (D/C)
OLED_RST: J3.44 (G2/BUS2), OLED1.7 (RST)
ROT_A: ENC1.A, R4.2, R6.2
ROT_B: ENC1.B, R5.2, R7.2
SCK: J3.57 (SPI_SCK), OLED1.4 (SCK), R13.2, U3.6 (SCK), U4.11 (ShiftClock/SCK), U5.11 (ShiftClock/SCK), U6.11 (ShiftClock/SCK), U7.11 (ShiftClock/SCK), U8.11 (ShiftClock/SCK), U9.6 (CLK)
SDIO_CLK: J3.60 (SPI_SCK1/SDIO_CLK), J4.5 (CLK)
SDIO_CMD: J3.62 (SPI_MOSI1/SDIO_CMD), J4.3 (CMD)
SDIO_DATA0: J3.64 (SPI_MISO1/SDIO_DATA0), J4.7 (DAT0)
SDIO_DATA1: J3.66 (SDIO_DATA1), J4.8 (DAT1)
SDIO_DATA2: J3.68 (SDIO_DATA2), J4.1 (DAT2)
SDIO_DATA3: J3.70 (SPI_~CS1/SDIO_DATA3), J4.2 (DAT3/CD)
SK6803_DAT_3V3: J3.32 (PWM0), U2.2
SK6803_DAT_5V: D35.2 (DIN), U2.4
SK6803_EN: J3.10 (D0), R2.1, U1.3 (EN)
SK6803_NFAULT: J3.12 (I2C_SDA), R1.2, U1.4 (~FAULT)
SK6803_PWR: C3.1, C4.1, C5.1, D1.3 (VDD), D2.3 (VDD), D3.3 (VDD), D4.3 (VDD), D5.3 (VDD), D6.3 (VDD), D7.3 (VDD), D8.3 (VDD), D9.3 (VDD), D10.3 (VDD), D11.3 (VDD), D12.3 (VDD), D13.3 (VDD), D14.3 (VDD), D15.3 (VDD), D16.3 (VDD), D17.3 (VDD), D18.3 (VDD), D19.3 (VDD), D20.3 (VDD), D21.3 (VDD), D22.3 (VDD), D23.3 (VDD), D24.3 (VDD), D25.3 (VDD), D26.3 (VDD), D27.3 (VDD), D28.3 (VDD), D29.3 (VDD), D30.3 (VDD), D31.3 (VDD), D32.3 (VDD), D33.3 (VDD), D34.3 (VDD), D35.3 (VDD), D36.3 (VDD), D37.3 (VDD), D38.3 (VDD), D39.3 (VDD), D40.3 (VDD), U1.6 (OUT), U2.5 (VCC)
SWCLK: J1.5, J3.21 (SWDCK)
SWDIO: J1.4, J3.23 (SWDIO)
SWO: J1.6, J3.8 (G11/SWO)
VBUS: D43.4 (VCC), F1.2, J2.A4 (VBUS), J2.A9 (VBUS), J2.B4 (VBUS), J2.B9 (VBUS)
VOLT_MEAS: J3.38 (A1), R12.1, R14.2
k00: RN1.8 (R1.2), SW1.2, U4.15 (A)
k01: RN1.7 (R2.2), SW11.2, U4.1 (B)
k02: RN1.6 (R3.2), SW21.2, U4.2 (C)
k03: RN1.5 (R4.2), SW31.2, U4.3 (D), U11.1 (1A)
k03&&k07: U11.3 (1Y), U11.12 (4A)
k04: RN2.4 (R4.1), SW2.2, U4.4 (E)
k05: RN2.3 (R3.1), SW12.2, U4.5 (F)
k06: RN2.2 (R2.1), SW22.2, U4.6 (G)
k07: RN2.1 (R1.1), SW32.2, U4.7 (H), U11.2 (1B)
k10: RN3.8 (R1.2), SW3.2, U5.15 (A)
k11: RN3.7 (R2.2), SW13.2, U5.1 (B)
k12: RN3.6 (R3.2), SW23.2, U5.2 (C)
k13: RN3.5 (R4.2), SW33.2, U5.3 (D), U11.4 (2A)
k13&&k17: U11.6 (2Y), U11.9 (3A)
k13&&k17&&k23: U11.8 (3Y), U11.13 (4B)
k14: RN4.4 (R4.1), SW4.2, U5.4 (E)
k15: RN4.3 (R3.1), SW14.2, U5.5 (F)
k16: RN4.2 (R2.1), SW24.2, U5.6 (G)
k17: RN4.1 (R1.1), SW34.2, U5.7 (H), U11.5 (2B)
k20: RN5.8 (R1.2), SW5.2, U6.15 (A)
k21: RN5.7 (R2.2), SW15.2, U6.1 (B)
k22: RN5.6 (R3.2), SW25.2, U6.2 (C)
k23: RN5.5 (R4.2), SW35.2, U6.3 (D), U11.10 (3B)
k24: RN6.4 (R4.1), SW6.2, U6.4 (E)
k25: RN6.3 (R3.1), SW16.2, U6.5 (F)
k26: RN6.2 (R2.1), SW26.2, U6.6 (G)
k27: RN6.1 (R1.1), SW36.2, U6.7 (H)
k30: RN7.8 (R1.2), SW7.2, U7.15 (A)
k31: RN7.7 (R2.2), SW17.2, U7.1 (B)
k32: RN7.6 (R3.2), SW27.2, U7.2 (C)
k33: RN7.5 (R4.2), SW37.2, U7.3 (D)
k34: RN8.4 (R4.1), SW8.2, U7.4 (E)
k35: RN8.3 (R3.1), SW18.2, U7.5 (F)
k36: RN8.2 (R2.1), SW28.2, U7.6 (G)
k37: RN8.1 (R1.1), SW38.2, U7.7 (H)
k40: RN9.8 (R1.2), SW9.2, U8.15 (A)
k41: RN9.7 (R2.2), SW19.2, U8.1 (B)
k42: RN9.6 (R3.2), SW29.2, U8.2 (C)
k43: RN9.5 (R4.2), SW39.2, U8.3 (D)
k44: RN10.4 (R4.1), SW10.2, U8.4 (E)
k45: RN10.3 (R3.1), SW20.2, U8.5 (F)
k46: RN10.2 (R2.1), SW30.2, U8.6 (G)
k47: RN10.1 (R1.1), SW40.2, U8.7 (H)
nBOOT: C19.1, D42.2 (A), J3.11 (~BOOT!), SW42.1
nRESET: D41.2 (A), J1.8, J3.6 (~RESET!), SW41.1
